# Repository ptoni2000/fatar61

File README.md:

# fatar61
Midi for Fatar 61 keys keyboard

This is a midi with blue pill board

The Midi interface is USB

Eagle directory contain schematic and pcb
Documentation contain some photos and videos of the board, box and cable

The keyboard is working wery well when connected to minisynt32: https://github.com/grantek/minisynth32

# NOTE: the actual firmware is on repository fatar61_tinyUSB !!!

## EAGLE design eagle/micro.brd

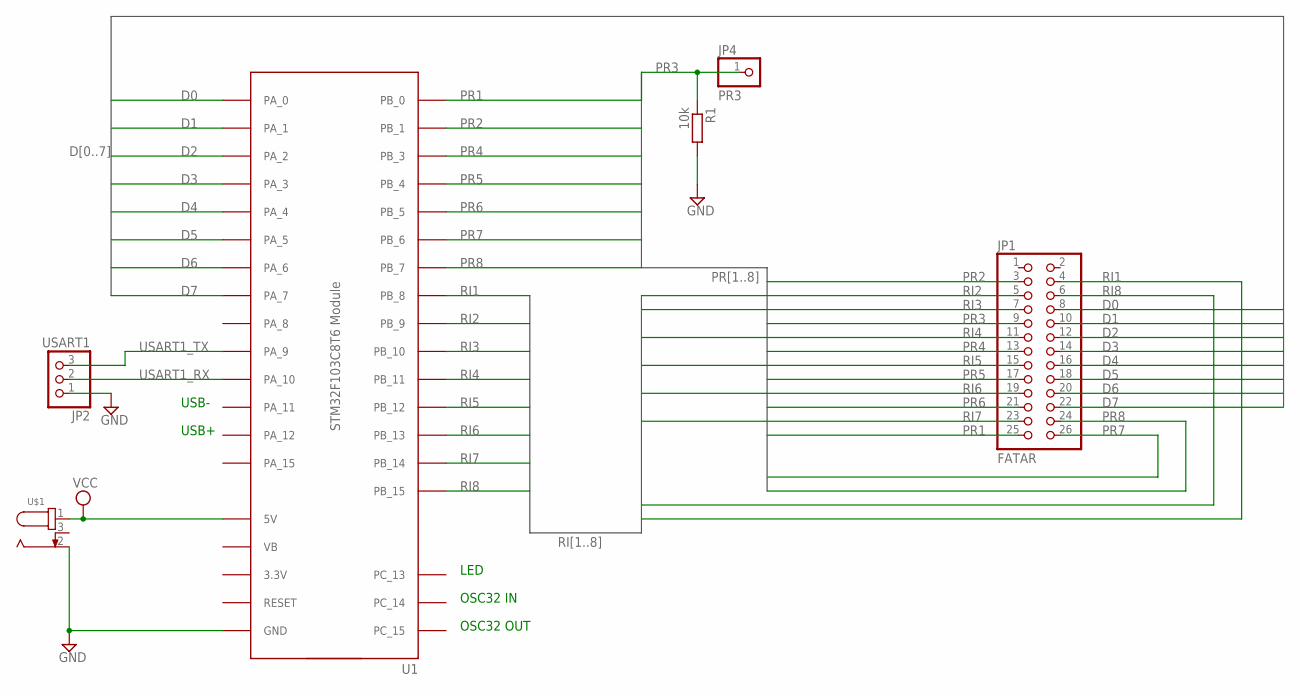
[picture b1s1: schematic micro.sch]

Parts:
JP1: FATAR; 2X13
JP2: USART1; 1X03
JP4: PR3; 1X01
R1: 10k; 0204/7
U1: STM32F103C8T6-MODULE
U$1: 694103303002

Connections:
D0: JP1.8, U1.PA_0
D1: JP1.10, U1.PA_1
D2: JP1.12, U1.PA_2
D3: JP1.14, U1.PA_3
D4: JP1.16, U1.PA_4
D5: JP1.18, U1.PA_5
D6: JP1.20, U1.PA_6
D7: JP1.22, U1.PA_7
GND: JP2.1, R1.2, U1.GND@1 (GND), U1.GND@2 (GND), U1.GND@3 (GND), U$1.2
PR1: JP1.25, U1.PB_0
PR2: JP1.3, U1.PB_1
PR3: JP1.9, JP4.1, R1.1
PR4: JP1.13, U1.PB_3
PR5: JP1.17, U1.PB_4
PR6: JP1.21, U1.PB_5
PR7: JP1.26, U1.PB_6
PR8: JP1.24, U1.PB_7
RI1: JP1.4, U1.PB_8
RI2: JP1.5, U1.PB_9
RI3: JP1.7, U1.PB_10
RI4: JP1.11, U1.PB_11
RI5: JP1.15, U1.PB_12
RI6: JP1.19, U1.PB_13
RI7: JP1.23, U1.PB_14
RI8: JP1.6, U1.PB_15
USART1_RX: JP2.2, U1.PA_10
USART1_TX: JP2.3, U1.PA_9
VCC: U1.5V, U$1.1

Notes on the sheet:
LED
OSC32 IN
OSC32 OUT
USB-
USB+

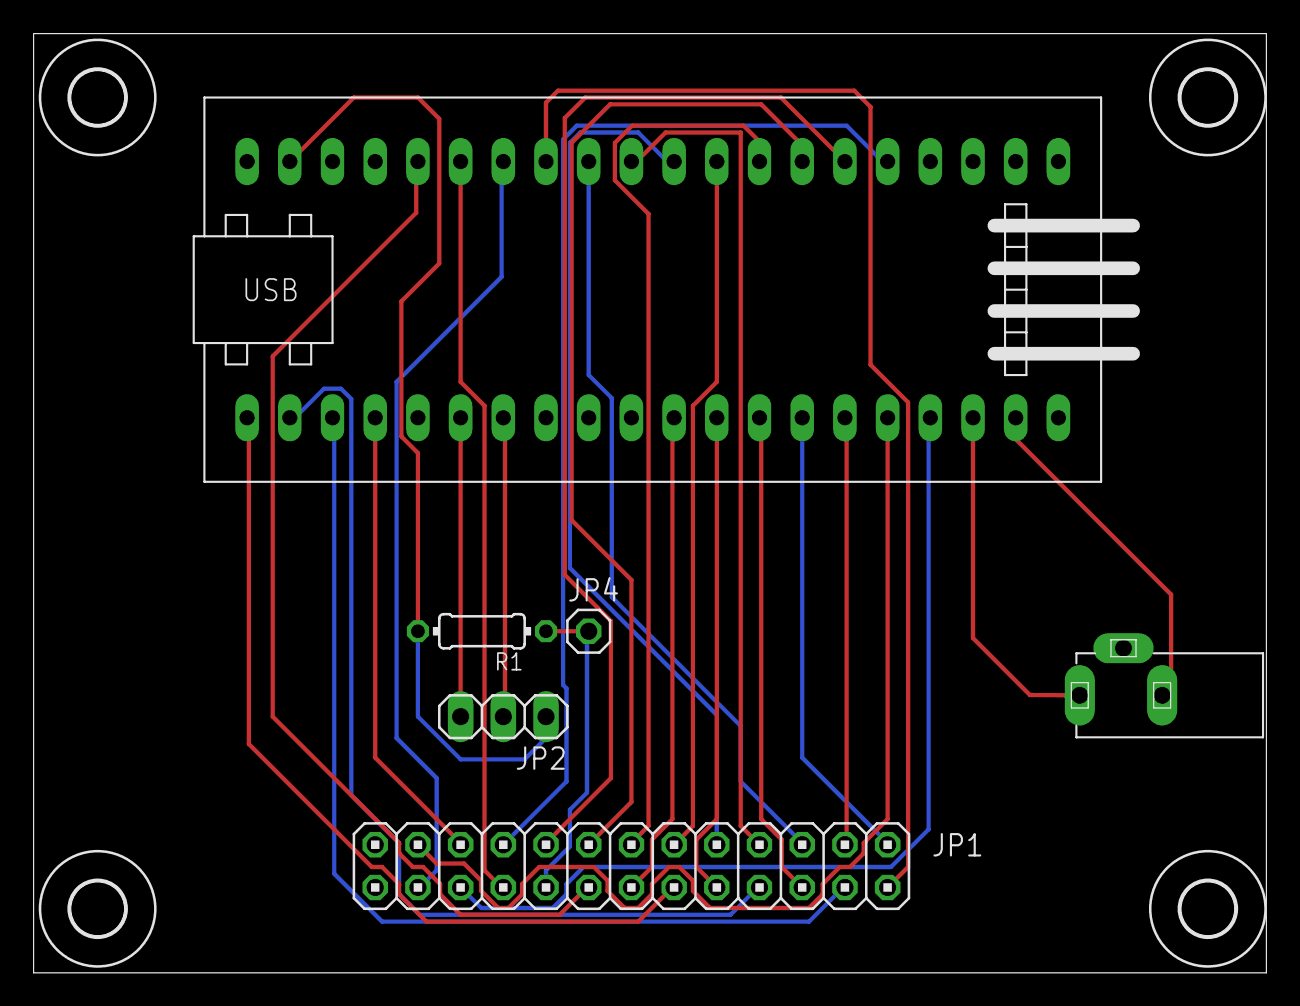
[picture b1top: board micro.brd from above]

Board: 2 copper layers, 73.3 x 55.9 mm, 10 parts (0 on the bottom side), 28 nets.

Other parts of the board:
U$2, U$3, U$4, U$5: 3,2

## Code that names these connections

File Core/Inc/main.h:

/* USER CODE BEGIN Header */
/**
  ******************************************************************************
  * @file           : main.h
  * @brief          : Header for main.c file.
  *                   This file contains the common defines of the application.
  ******************************************************************************
  * @attention
  *
  * <h2><center>&copy; Copyright (c) 2021 STMicroelectronics.
  * All rights reserved.</center></h2>
  *
  * This software component is licensed by ST under BSD 3-Clause license,
  * the "License"; You may not use this file except in compliance with the
  * License. You may obtain a copy of the License at:
  *                        opensource.org/licenses/BSD-3-Clause
  *
  ******************************************************************************
  */
/* USER CODE END Header */

/* Define to prevent recursive inclusion -------------------------------------*/
#ifndef __MAIN_H
#define __MAIN_H

#ifdef __cplusplus
extern "C" {
#endif

/* Includes ------------------------------------------------------------------*/
#include "stm32f1xx_hal.h"

/* Private includes ----------------------------------------------------------*/
/* USER CODE BEGIN Includes */

/* USER CODE END Includes */

/* Exported types ------------------------------------------------------------*/
/* USER CODE BEGIN ET */

/* USER CODE END ET */

/* Exported constants --------------------------------------------------------*/
/* USER CODE BEGIN EC */
extern TIM_HandleTypeDef htim1;
extern TIM_HandleTypeDef htim2;
/* USER CODE END EC */

/* Exported macro ------------------------------------------------------------*/
/* USER CODE BEGIN EM */

/* USER CODE END EM */

/* Exported functions prototypes ---------------------------------------------*/
void Error_Handler(void);

/* USER CODE BEGIN EFP */

/* USER CODE END EFP */

/* Private defines -----------------------------------------------------------*/
#define LED_Pin GPIO_PIN_13
#define LED_GPIO_Port GPIOC
#define D0_Pin GPIO_PIN_0
#define D0_GPIO_Port GPIOA
#define D1_Pin GPIO_PIN_1
#define D1_GPIO_Port GPIOA
#define D2_Pin GPIO_PIN_2
#define D2_GPIO_Port GPIOA
#define D3_Pin GPIO_PIN_3
#define D3_GPIO_Port GPIOA
#define D4_Pin GPIO_PIN_4
#define D4_GPIO_Port GPIOA
#define D5_Pin GPIO_PIN_5
#define D5_GPIO_Port GPIOA
#define D6_Pin GPIO_PIN_6
#define D6_GPIO_Port GPIOA
#define D7_Pin GPIO_PIN_7
#define D7_GPIO_Port GPIOA
#define PR1_Pin GPIO_PIN_0
#define PR1_GPIO_Port GPIOB
#define PR2_Pin GPIO_PIN_1
#define PR2_GPIO_Port GPIOB
#define PR3_Pin GPIO_PIN_2
#define PR3_GPIO_Port GPIOB
#define RI3_Pin GPIO_PIN_10
#define RI3_GPIO_Port GPIOB
#define RI4_Pin GPIO_PIN_11
#define RI4_GPIO_Port GPIOB
#define RI5_Pin GPIO_PIN_12
#define RI5_GPIO_Port GPIOB
#define RI6_Pin GPIO_PIN_13
#define RI6_GPIO_Port GPIOB
#define RI7_Pin GPIO_PIN_14
#define RI7_GPIO_Port GPIOB
#define RI8_Pin GPIO_PIN_15
#define RI8_GPIO_Port GPIOB
#define PR4_Pin GPIO_PIN_3
#define PR4_GPIO_Port GPIOB
#define PR5_Pin GPIO_PIN_4
#define PR5_GPIO_Port GPIOB
#define PR6_Pin GPIO_PIN_5
#define PR6_GPIO_Port GPIOB
#define PR7_Pin GPIO_PIN_6
#define PR7_GPIO_Port GPIOB
#define PR8_Pin GPIO_PIN_7
#define PR8_GPIO_Port GPIOB
#define RI1_Pin GPIO_PIN_8
#define RI1_GPIO_Port GPIOB
#define RI2_Pin GPIO_PIN_9
#define RI2_GPIO_Port GPIOB
/* USER CODE BEGIN Private defines */

/* USER CODE END Private defines */

#ifdef __cplusplus
}
#endif

#endif /* __MAIN_H */

/************************ (C) COPYRIGHT STMicroelectronics *****END OF FILE****/

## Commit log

2021-08-09 Importati files midi, conf. gpio
2021-08-09 aggiunta dir MAin, compila.
2021-08-18 Add timer1 for delay_us
2021-08-18 Add USB irq handler.
2021-08-18 Add retarget printf on USART1
2021-08-18 Add key up/down code.
2021-08-18 key map correct.
2021-10-18 Chiamata dal timer2 ogni millisecondo
2021-10-18 USB device hard reset
2021-10-18 funziona ma perde messaggi.
2021-10-19 Scan in loop, non in timer
2021-10-19 USB_DEVICE da stm32f4-midi-brain
2021-10-19 Maste hard reset USB
2021-10-20 encoder collegato su piedini uart.
2023-03-01 Added documentation, schematic and pictures.
